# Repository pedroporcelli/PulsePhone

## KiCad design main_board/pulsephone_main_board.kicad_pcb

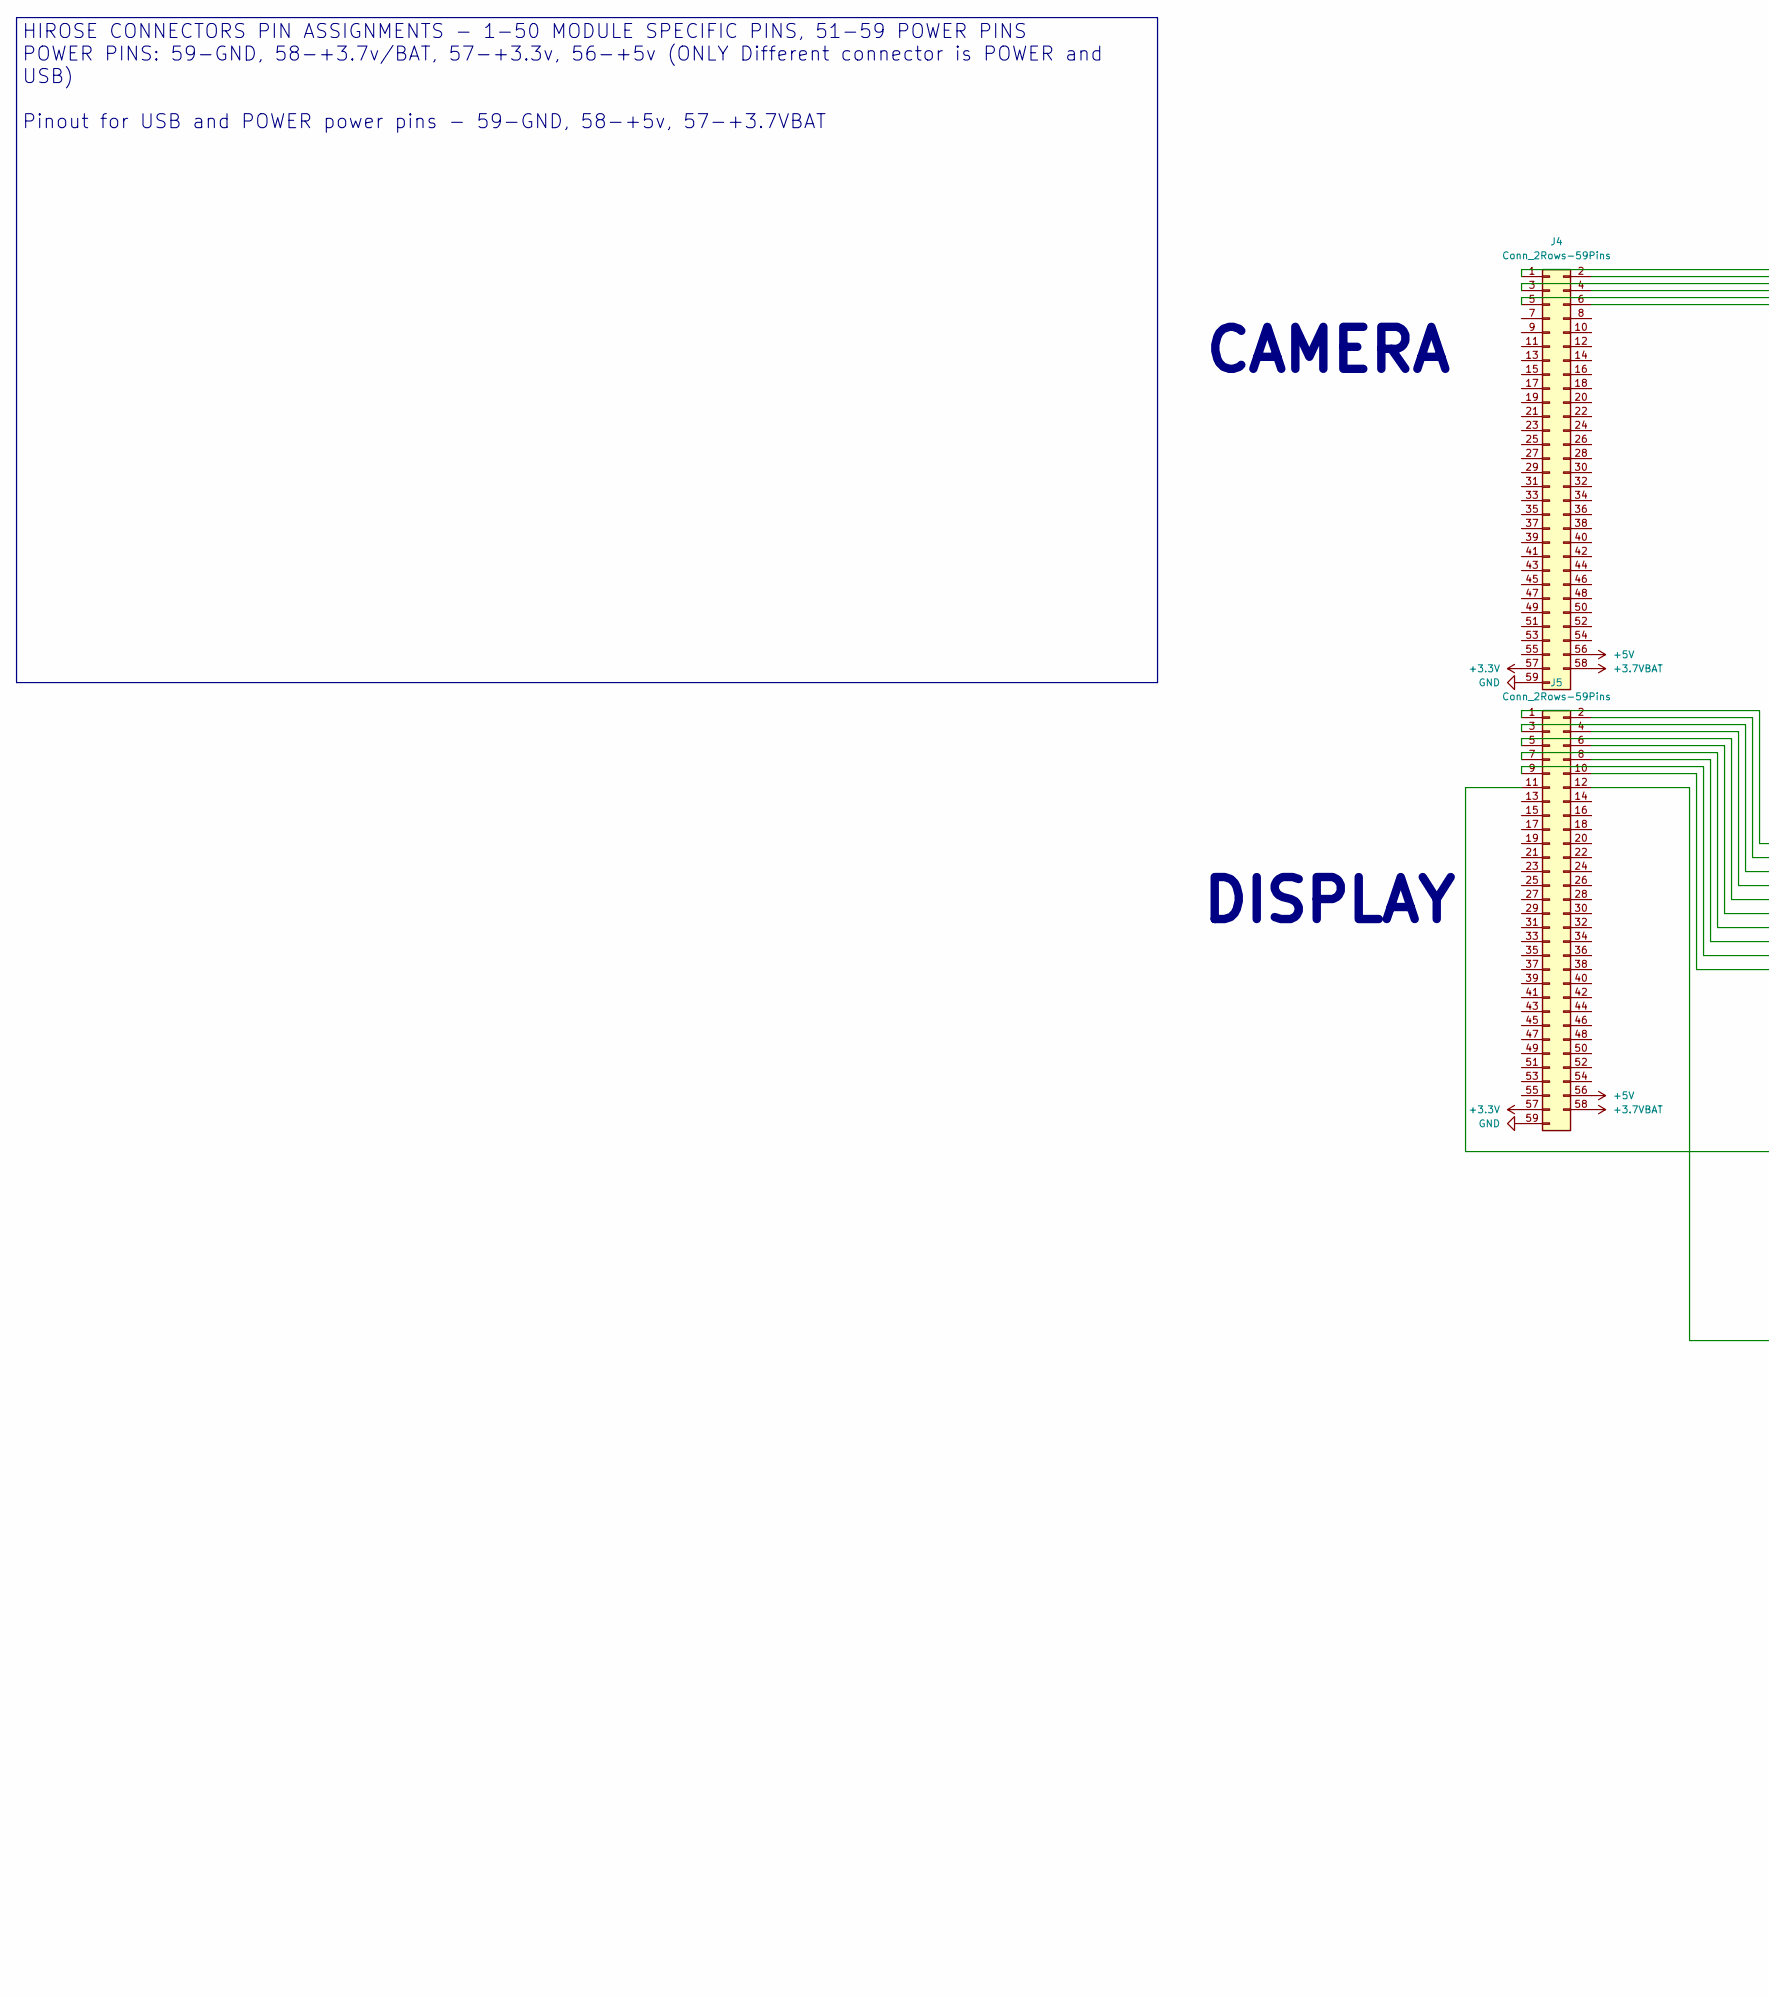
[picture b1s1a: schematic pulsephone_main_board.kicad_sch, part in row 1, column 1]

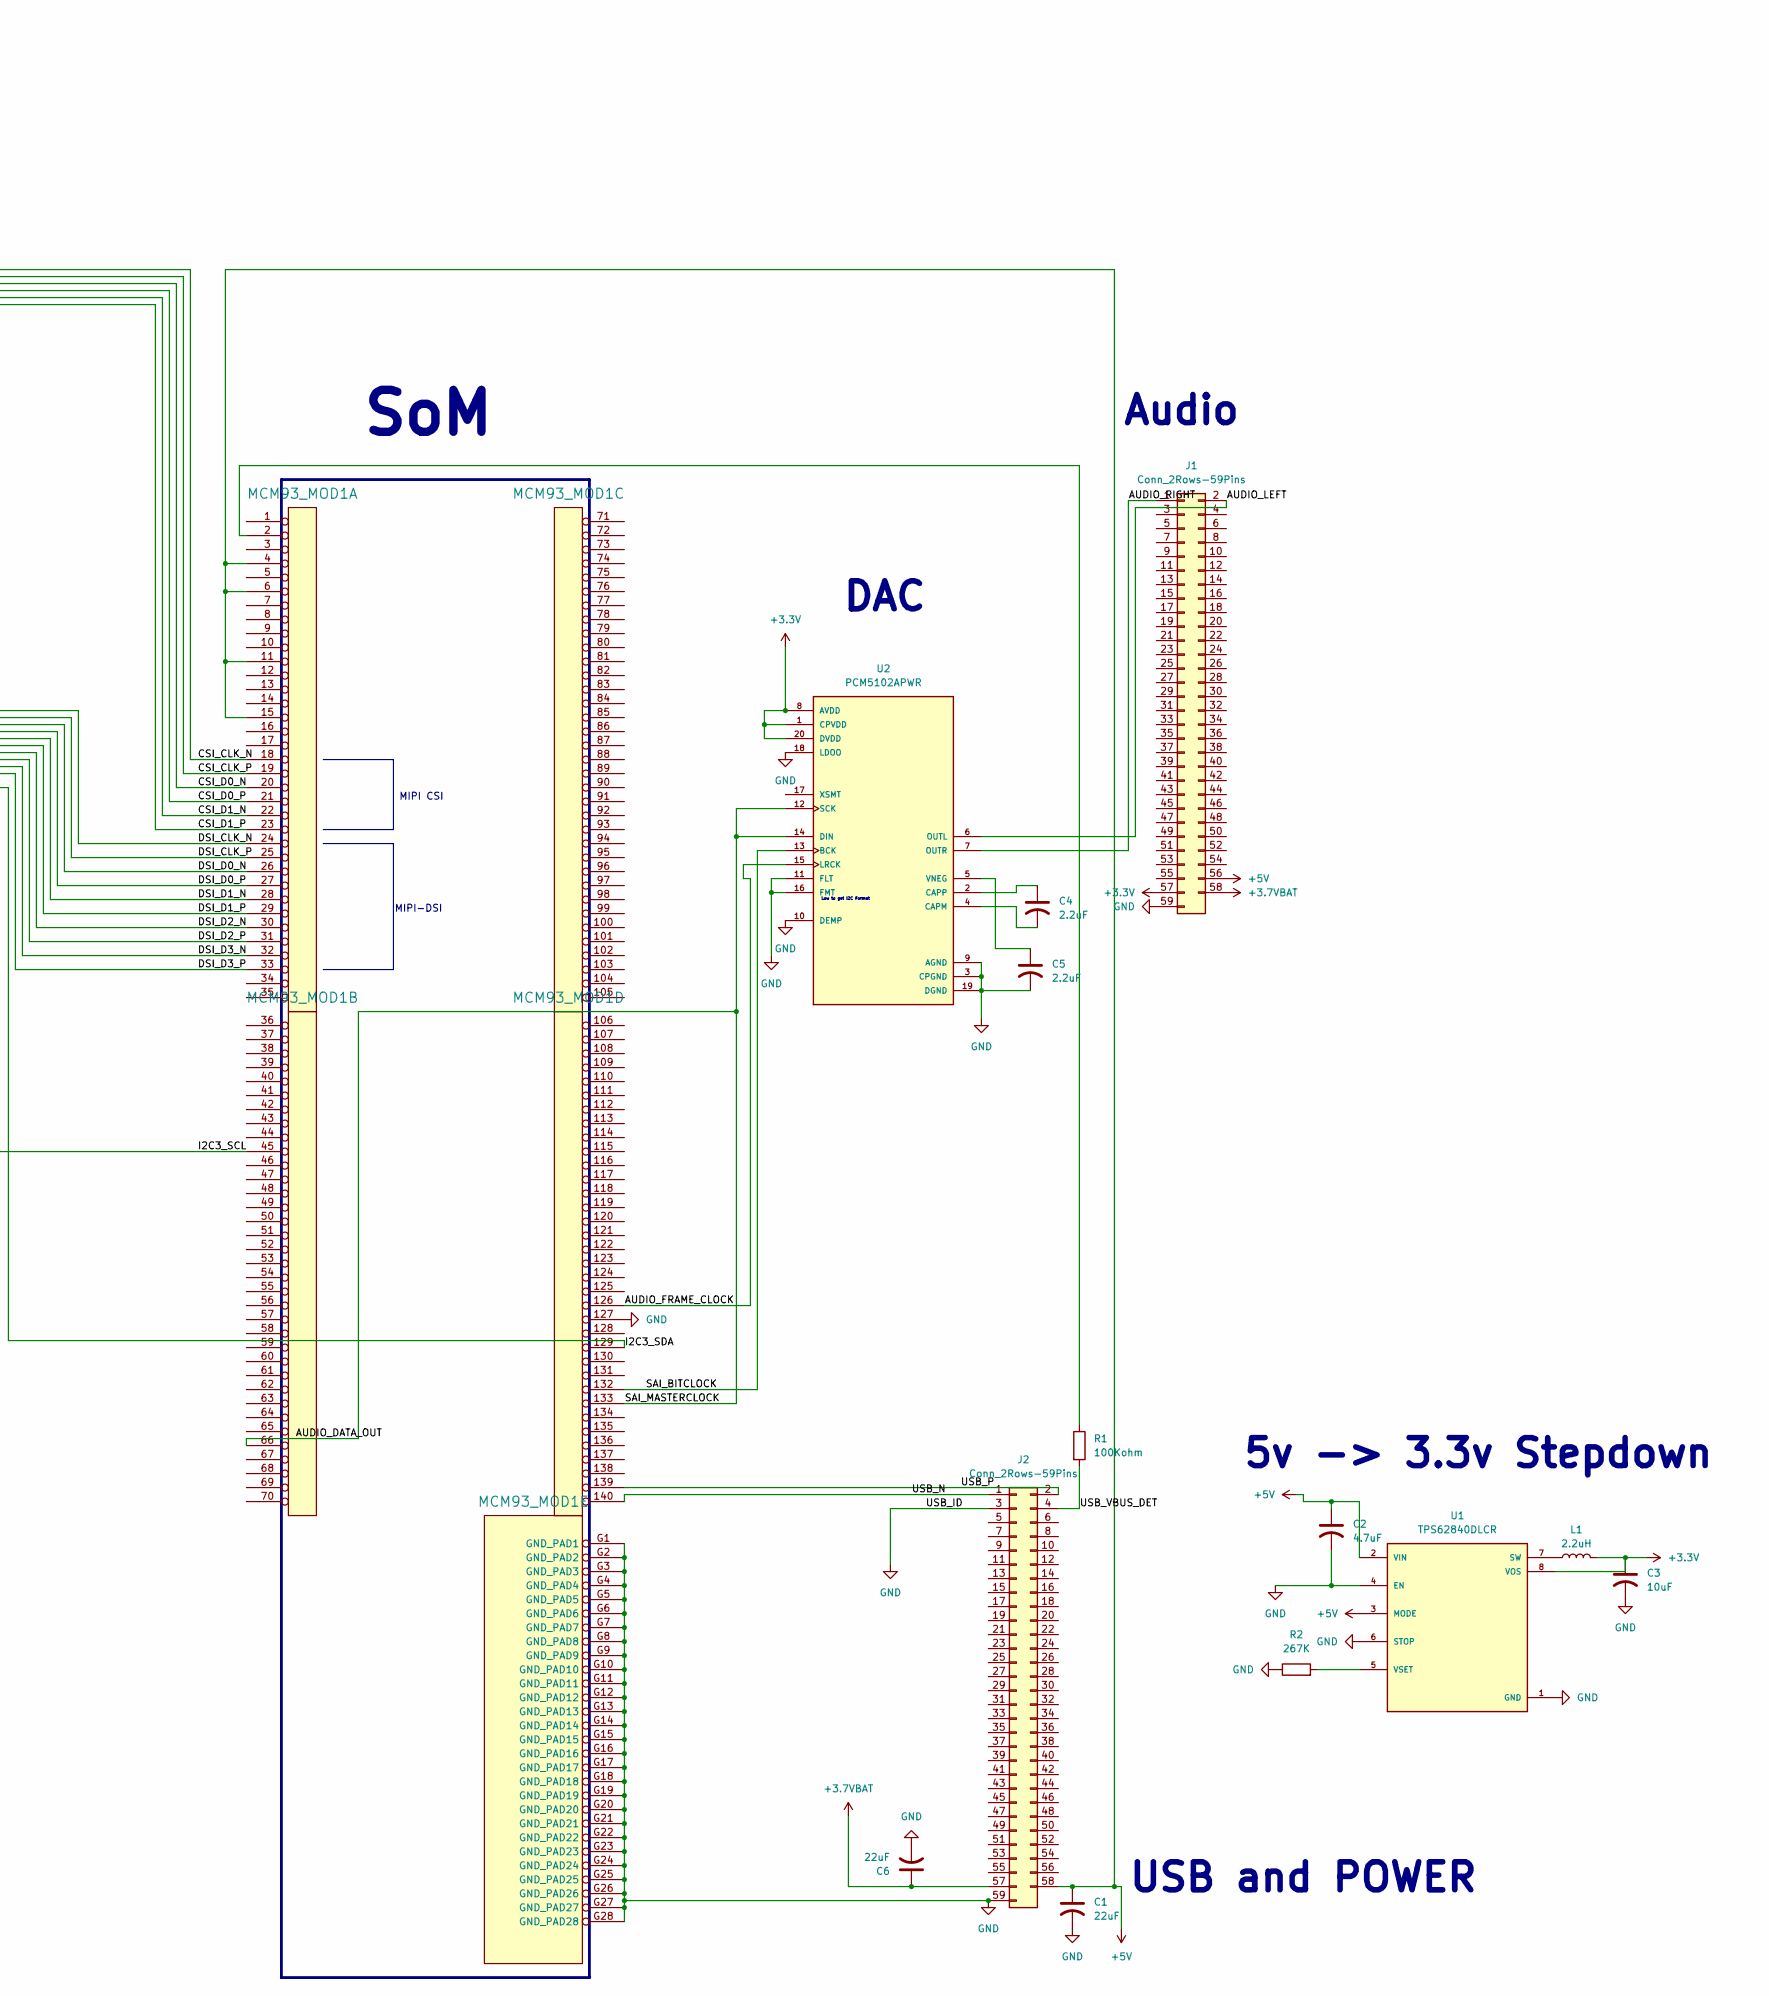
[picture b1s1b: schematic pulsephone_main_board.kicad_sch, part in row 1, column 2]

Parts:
C1, C6: 22uF; C_0805_2012Metric
C2: 4.7uF; C_0805_2012Metric
C3: 10uF; C_0805_2012Metric
C4, C5: 2.2uF; C_0805_2012Metric
J1, J2, J4, J5: Conn_2Rows-59Pins; Hirose_DF12_DF12E3.0-60DP-0.5V_2x30_P0.50mm_Vertical
L1: 2.2uH; L_0805_2012Metric
MCM93_MOD1: MCM93_MOD; LGA-140-080-30x30-iMX93
R1: 100Kohm; R_0805_2012Metric
R2: 267K; R_0805_2012Metric
U1: TPS62840DLCR; SON50P200X150X100-8N
U2: PCM5102APWR; SOP65P640X120-20N; PARTREV C

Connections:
+3.3V: C3.1, J1.57, J4.57, J5.57, L1.2, U1.8 (VOS), U2.1 (CPVDD), U2.8 (AVDD), U2.20 (DVDD)
+3.7VBAT: C6.1, J1.58, J2.57, J4.58, J5.58
+5V: C1.1, C2.1, J1.56, J2.58, J4.56, J5.56, MCM93_MOD1.4, MCM93_MOD1.6, MCM93_MOD1.11, MCM93_MOD1.15, U1.2 (VIN), U1.3 (MODE)
/AUDIO_DATA_OUT: MCM93_MOD1.66 (31), MCM93_MOD1.133 (28), U2.12 (SCK), U2.14 (DIN)
/AUDIO_FRAME_CLOCK: MCM93_MOD1.126 (21), U2.15 (LRCK)
/AUDIO_LEFT: J1.2, U2.6 (OUTL)
/AUDIO_RIGHT: J1.1, U2.7 (OUTR)
/CSI_CLK_N: J4.1, MCM93_MOD1.18
/CSI_CLK_P: J4.2, MCM93_MOD1.19
/CSI_D0_N: J4.3, MCM93_MOD1.20
/CSI_D0_P: J4.4, MCM93_MOD1.21
/CSI_D1_N: J4.5, MCM93_MOD1.22
/CSI_D1_P: J4.6, MCM93_MOD1.23
/DSI_CLK_N: J5.1, MCM93_MOD1.24
/DSI_CLK_P: J5.2, MCM93_MOD1.25
/DSI_D0_N: J5.3, MCM93_MOD1.26
/DSI_D0_P: J5.4, MCM93_MOD1.27
/DSI_D1_N: J5.5, MCM93_MOD1.28
/DSI_D1_P: J5.6, MCM93_MOD1.29
/DSI_D2_N: J5.7, MCM93_MOD1.30
/DSI_D2_P: J5.8, MCM93_MOD1.31
/DSI_D3_N: J5.9, MCM93_MOD1.32
/DSI_D3_P: J5.10, MCM93_MOD1.33
/I2C3_SCL: J5.11, MCM93_MOD1.45 (10)
/I2C3_SDA: J5.12, MCM93_MOD1.129 (24)
/SAI_BITCLOCK: MCM93_MOD1.132 (27), U2.13 (BCK)
/USB_N: J2.1, MCM93_MOD1.140 (35)
/USB_P: J2.2, MCM93_MOD1.139 (34)
/USB_VBUS_DET: J2.4, R1.2
GND: C1.2, C2.2, C3.2, C5.2, C6.2, J1.59, J2.3, J2.59, J4.59, J5.59, MCM93_MOD1.127 (22), MCM93_MOD1.G1 (GND_PAD1), MCM93_MOD1.G2 (GND_PAD2), MCM93_MOD1.G3 (GND_PAD3), MCM93_MOD1.G4 (GND_PAD4), MCM93_MOD1.G5 (GND_PAD5), MCM93_MOD1.G6 (GND_PAD6), MCM93_MOD1.G7 (GND_PAD7), MCM93_MOD1.G8 (GND_PAD8), MCM93_MOD1.G9 (GND_PAD9), MCM93_MOD1.G10 (GND_PAD10), MCM93_MOD1.G11 (GND_PAD11), MCM93_MOD1.G12 (GND_PAD12), MCM93_MOD1.G13 (GND_PAD13), MCM93_MOD1.G14 (GND_PAD14), MCM93_MOD1.G15 (GND_PAD15), MCM93_MOD1.G16 (GND_PAD16), MCM93_MOD1.G17 (GND_PAD17), MCM93_MOD1.G18 (GND_PAD18), MCM93_MOD1.G19 (GND_PAD19), MCM93_MOD1.G20 (GND_PAD20), MCM93_MOD1.G21 (GND_PAD21), MCM93_MOD1.G22 (GND_PAD22), MCM93_MOD1.G23 (GND_PAD23), MCM93_MOD1.G24 (GND_PAD24), MCM93_MOD1.G25 (GND_PAD25), MCM93_MOD1.G26 (GND_PAD26), MCM93_MOD1.G27 (GND_PAD27), MCM93_MOD1.G28 (GND_PAD28), R2.1, U1.1 (GND), U1.4 (EN), U1.6 (STOP), U2.3 (CPGND), U2.9 (AGND), U2.10 (DEMP), U2.11 (FLT), U2.16 (FMT), U2.18 (LDOO), U2.19 (DGND)
unnamed: MCM93_MOD1.2, R1.1
unnamed: L1.1, U1.7 (SW)
unnamed: R2.2, U1.5 (VSET)
unnamed: C4.2, U2.4 (CAPM)
unnamed: C4.1, U2.2 (CAPP)
unnamed: C5.1, U2.5 (VNEG)

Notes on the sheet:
MIPI CSI
DAC
SoM
MIPI-DSI
5v -> 3.3v Stepdown
USB and POWER
Audio
Low to get I2C Format
DISPLAY
CAMERA
HIROSE CONNECTORS PIN ASSIGNMENTS - 1-50 MODULE SPECIFIC PINS, 51-59 POWER PINS POWER PINS: 59-GND, 58-+3.7v/BAT, 57-+3.3v, 56-+5v (ONLY Different connector is POWER and USB) Pinout for USB and POWER power pins - 59-GND, 58-+5v, 57-+3.7VBAT

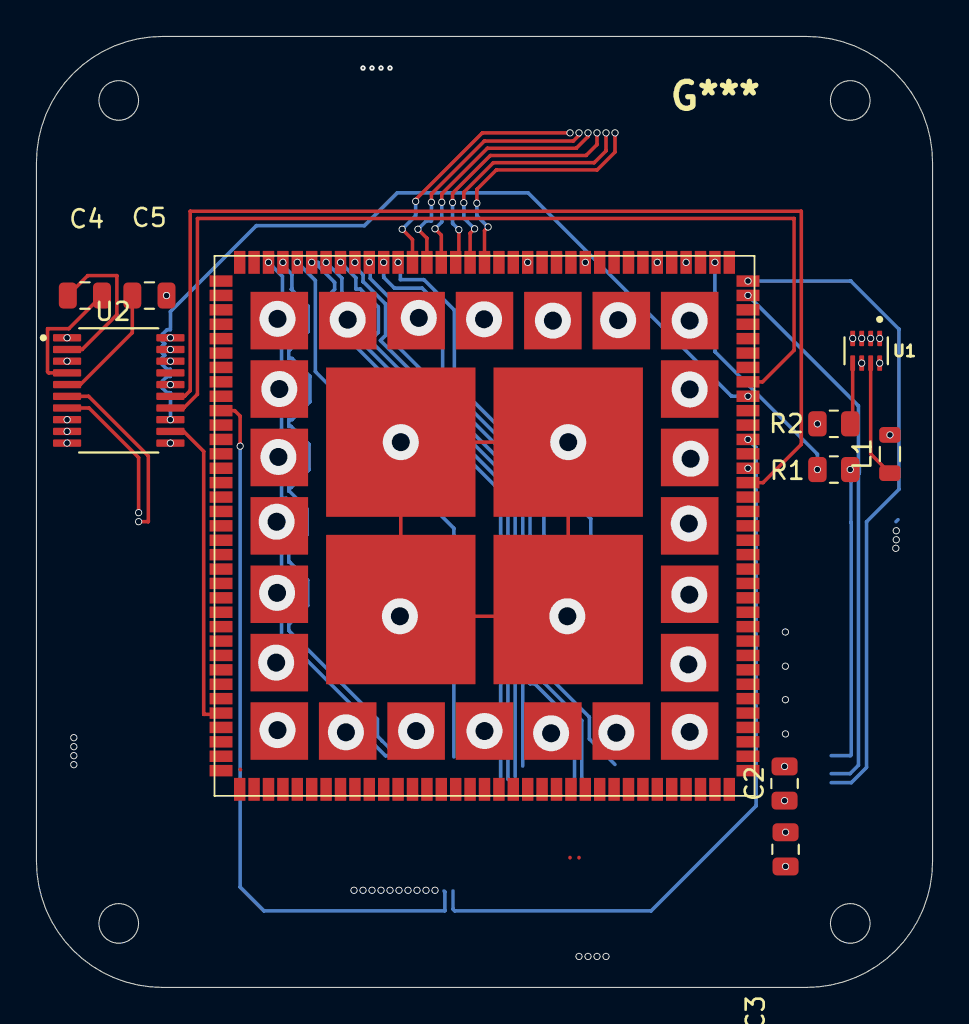
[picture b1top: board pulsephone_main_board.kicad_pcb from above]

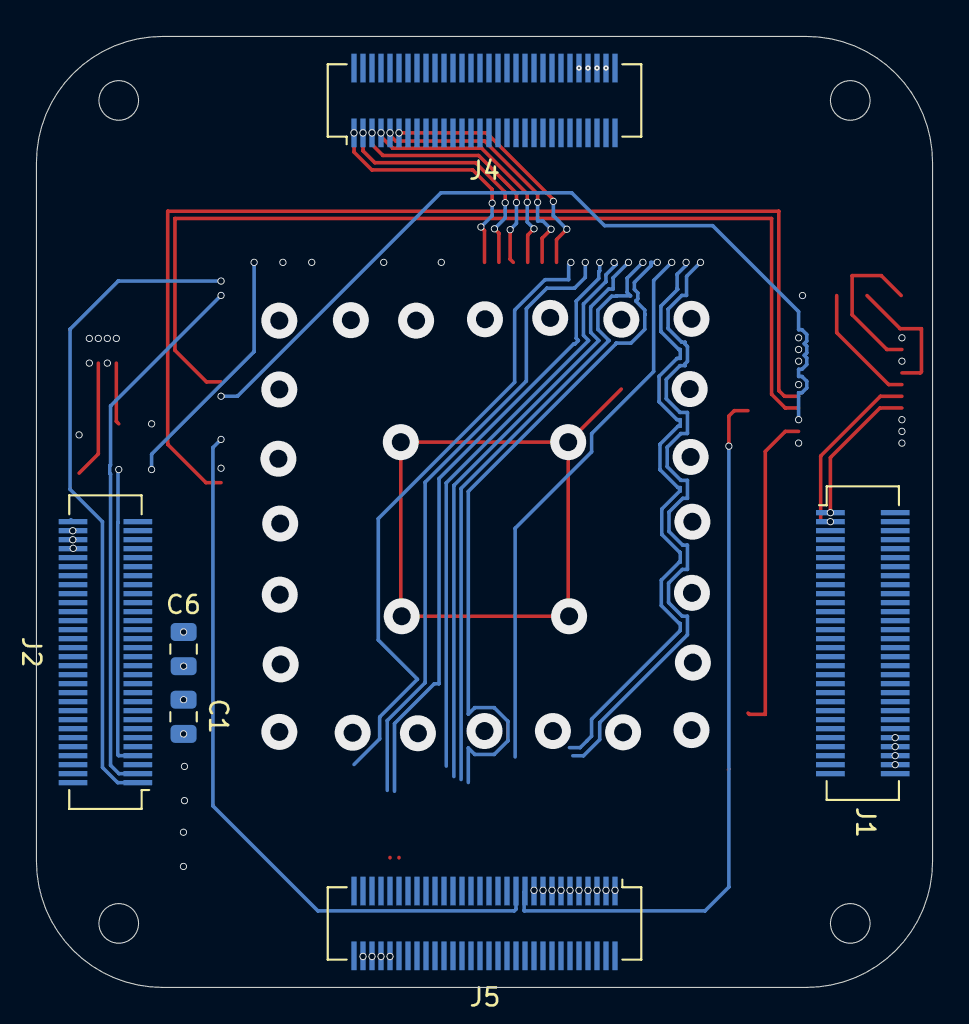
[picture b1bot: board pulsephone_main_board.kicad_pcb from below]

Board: 6 copper layers, 49.8 x 52.8 mm, 16 parts (6 on the bottom side), 36 nets.

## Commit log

2025-09-28 Add KiCad Files
2025-09-29 Add battery module
    Battery module is WIP.
2025-09-29 Put connectors in correct orientation
    Connectors where in the wrong orientation. Reminder: Rewire DSI-MIPI connections on pcb!
2025-09-29 Added connectors in correct orientation.
